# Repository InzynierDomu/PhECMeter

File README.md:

# PhECMeter

- [PhECMeter](#phecmeter)
  - [Description](#description)
    - [Future](#future)
  - [Scheme](#scheme)
    - [Part list](#part-list)
  - [IDE](#ide)
  - [Quick deployment without using VS Code environment](#quick-deployment-without-using-vs-code-environment)
    - [Requirements](#requirements)
    - [Usage](#usage)
    - [Notes](#notes)

## Description
The video with the entire project can be watched on this [video](https://youtu.be/vjk0nq04lCo)

The device has 4 possible states:
* measure pH
* measure EC
* calibartion pH
* calibration EC

The device start in pH measure mode. To chnage pH/EC measure mode - press up button for more than 1s.</br>
To enter calibration mode press both buttons more 1s.</br>
Measure pH -> calibration pH.</br>
Measure EC -> calibartion EC.</br>
Calibration mode needs 2 points to save.</br>
Set the value to which sample the probe is immersed. For that use up and dwn(down) buttons to decrease or increase the value. In EC calibration possible is to change the digit position by pressing 1s up button. To save points press 1s on both buttons. After saving two points, the device changes state to measure.</br>
</br>
When SD card is plugged, after short press down button measurements will be save in file on SD.

<div align="center">
<h2>Support</h2>

<p>If any of my projects have helped you in your work, studies, or simply made your day better, you can buy me a coffee. </p>
</div>

### Future
* Use accumulator.
* Add some communication maybe RS232 or RS485.

## Scheme

### Part list
* pH probe and board like [this](https://botland.com.pl/pl/seria-gravity/15094-gravity-czujnik-miernik-ph-analogowy-v2-dfrobot-sen0161-v2.html?utm_source=blog&utm_medium=link&utm_campaign=inzynierdomu)
* EC probe and board like [this](https://botland.com.pl/gravity-czujniki-pogodowe/15096-gravity-analogowy-czujnik-zasolenia-wody-i-gleby-dfrobot-dfr0300-h-5904422348359.html?utm_source=blog&utm_medium=link&utm_campaign=inzynierdomu)
* A1 Arduino Nano
* U1 ds18b20 temperature sensor
* J1 is socket for pH board.
* J2 is socket for I2C screen OLED SSD1306 128x32 or HD44780 via PCF8574. 
* R1 Resistor 4,7 kohm
* SW1, SW2 micro switch
* SW3 switch to turning on/of power
* J3 connect to battery box
* J5 SD card socket (optional)

## IDE
If you prefer not to use the VS Code environment or prefer simpler solutions, you can use an [alternative approach](#quick-deployment-without-using-vs-code-environment)
For specific screen is the prepared environment:</br>
OLED SSD1306 128x32 :nanoatmega328_oled</br>
HD44780 via PCF8574 :nanoatmega328_lcd</br>
</br>
The project is prepared for the Platform IO environment. A video on how to install such an environment can be watched on this [video](https://youtu.be/Em9NuebT2Kc).
<br><br>
Formatting is done using clang-format. The description of the tool configuration is in the [video](https://youtu.be/xxuaOG0WjIE).
<br><br>
The code contains a comment prepared for doxygen, their use is described in the [video](https://youtu.be/1YKJtrCsPD4).

## Quick deployment without using VS Code environment
You don't need vscode, platformio is not needed, it will be installed with the script.

### Requirements
* Python 3.x must be installed on your computer. You can download the latest version of Python from Python.org.
### Usage
* Connect the Arduino board to your computer using a USB cable.
* Ensure that Python is available in the system environment.
* Run the autodeploy.bat file by double-clicking on it or running it from the command prompt (cmd). This script will automatically detect the connected Arduino board and upload the project to it.
### Notes
* It's version for oled.
* Make sure that the path to Python is added to the PATH environment variable in the Windows operating system.
* The atodeploy.bat script works only on Windows.

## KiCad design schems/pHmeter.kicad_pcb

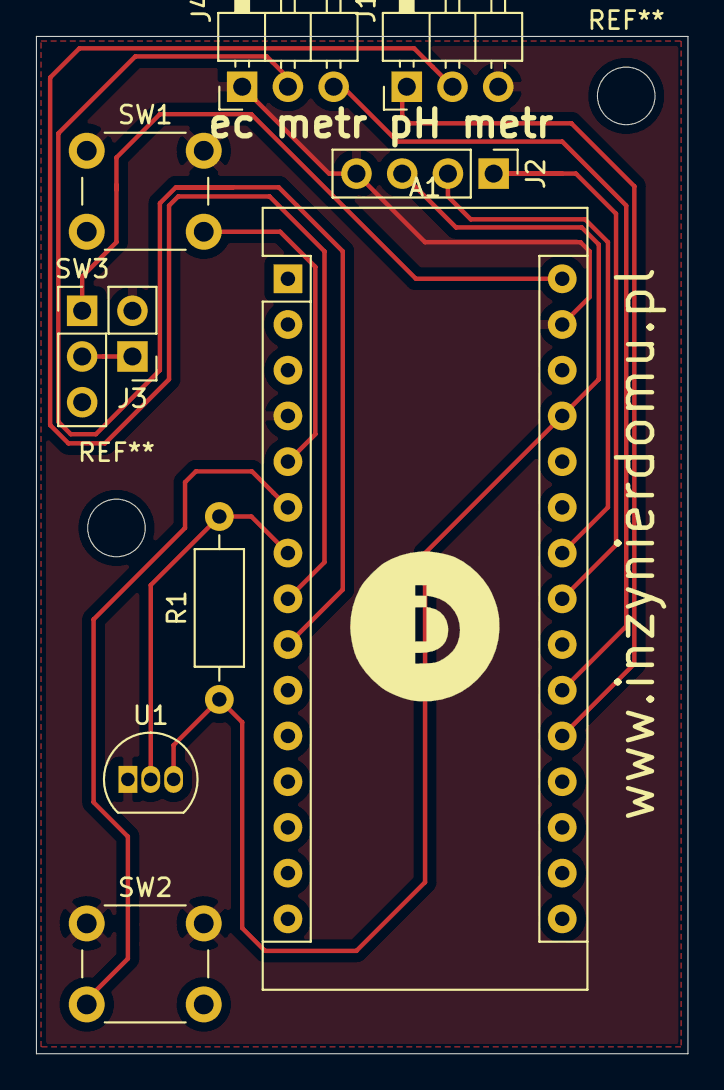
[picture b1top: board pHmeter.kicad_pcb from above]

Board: 2 copper layers, 36.2 x 56.5 mm, 10 parts (0 on the bottom side), 13 nets.

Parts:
A1: Arduino_Nano_v3.x; Arduino_Nano
J1, J4: Conn_01x03_Male; PinHeader_1x03_P2.54mm_Horizontal
J2: Conn_01x04; PinHeader_1x04_P2.54mm_Vertical
J3: Conn_01x02; PinHeader_1x02_P2.54mm_Vertical
R1: 4,7K; R_Axial_DIN0207_L6.3mm_D2.5mm_P10.16mm_Horizontal
SW1, SW2: SW_Push; SW_PUSH_6mm_H8mm
SW3: SW_SPDT; PinHeader_1x03_P2.54mm_Vertical
U1: DS18B20; TO-92_Inline

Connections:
+5V: A1.27, J2.3, R1.1, U1.3
+9V: A1.30, SW3.1
+BATT: J3.1, SW3.2
Data: A1.7, R1.2, U1.2
EC_vcc: A1.9, J4.2
GND: A1.4, A1.29, J1.3, J2.4, J3.2, J4.1, SW1.1, SW2.1, U1.1
unnamed: A1.5, SW1.2
unnamed: A1.6, SW2.2
unnamed: A1.20, J1.1
unnamed: A1.21, J4.3
unnamed: A1.23, J2.1
unnamed: A1.24, J2.2
Ph_vcc: A1.8, J1.2

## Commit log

2020-09-24 create repository
2020-11-21 move liner function and add smal delay to easy calibration
2021-01-04 Add pin to supply ph sonde
2021-01-04 Update README.md
    update schem
2021-05-15 Add state machine
2021-05-16 add ec metr and button actions
2021-06-02 move memeory load/save
2022-06-13 update pio and add clang format
2022-06-14 add CI
2022-06-14 add check env
2022-06-20 fix changing mode ec/ph
2022-06-20 add ec pins
2022-06-20 remove arduino stl
2022-06-21 doxygen
2022-06-21 add doxgen build and founding
2022-06-21 remove lib deps from repo
2022-06-21 update gfx lib
2022-06-21 Create LICENSE
2022-06-22 chang point type in memory
2022-06-23 add EC calibration
2022-06-24 fix unit
2022-06-24 manual
2022-07-05 add max value
2022-07-06 simplification save nad load calibartion
2022-07-11 update buttons names
2022-07-28 Move button handling to other files
2022-07-29 split check to small functions
2022-08-01 fix button naming
2022-08-01 add lcd env
2022-08-02 add libs
2022-08-02 add schems
2022-08-02 add clang-tidy
2022-08-04 clang-format
2022-08-10 split to two screen class
2022-08-13 lcd running
2022-08-14 add SD lib
2022-08-16 fix names
2022-08-16 format save data
2022-08-24 test other oled screen
2022-08-26 fix main buttons issues
2022-08-29 update schem
2022-08-29 delay move
2022-08-30 update calibration
2022-09-02 fix calib mode screen
2022-09-02 save calibration fix
2022-09-02 update uml
2022-09-07 clean buttons actions
2022-09-10 change in oled libary, add degree instead '
2022-09-12 clear
2022-09-12 remove old env
2022-09-12 update degree symbol
2022-09-12 fix sd rebase
2022-09-13 fix ec calibration
2022-09-13 add plantuml job
2022-09-13 change path uml
2022-09-13 clear folders
2022-09-13 add rotation screen
2022-09-13 Render PlantUML files
2022-09-14 change docs file
2022-09-14 Update Doxyfile
2022-09-19 add new api function
2022-09-19 add states to machine
2022-09-19 add memory map
2022-09-19 change interrupts
2022-09-20 extended main state chart for new automation
2022-09-20 fill automation
2022-09-27 fix button reaction
2022-10-02 rm not tracking file
2022-10-02 remove old index docs
2022-10-10 fix interrupts
2022-10-11 add ph range change
2022-10-14 add check min ph
2022-10-14 add fill functions
2022-10-14 add checking ph and ec min value
2022-10-14 fix toggle char in set range ph
2022-10-17 fix pins with sd card (sd card disable)
2022-10-17 add enable to automation
2022-10-18 add print calibration data on start
2022-10-21 add manual
2022-10-21 fix build
2022-10-22 change naming
2022-10-24 add longer measurments
2023-01-12 fix shield
2023-06-10 change y,x value to unit and analog value naming
2023-06-20 update doxy description
2023-06-21 add class brif for dox
2023-08-04 add brief
2023-08-04 fix naming
2023-10-01 change schem
2023-10-01 deploy: 8631dabed188db58a08b94a5af596527d4656c74
2024-04-21 change naming and constructor linear function points
2024-04-21 fix checkusm
2024-04-26 add load old values in calibration mode
2024-04-26 fix next load old values in calibration mode
2024-04-29 add autodeploy script
2024-04-29 add documentation for autodeploy script
2024-04-29 update autodeploy script
2024-05-27 add loging autodeploy script
2024-05-31 split echos
2024-05-31 fix autodeploy path
2024-05-31 add upload log
2024-06-02 modify git ignore
2024-06-12 fix autodeploy
2024-06-13 add the ability to decide what env
2024-06-19 change platformio run
2025-03-06 update founding
2025-03-06 update CI
2025-03-07 deploy: f14d21cf1a27d8bf87f5d7d15fd82aa16b4ac5b0
